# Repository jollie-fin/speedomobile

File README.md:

# Introduction

This project goal is to have a fun plateform to showcase the following :

- sensor fusion
- persistence of vision
- spatial pollution measurement
- video stream enhancement
- non trivial Rust project
- PCB design

It consists, in a way, in a "let's put every components I can find" kind of project

# Firmware

To be done

# 3D printing

Some care will be taken to properly protect components from the rain

To be done

# Hardware

On the hardware side, four boards have been designed

## Main board

This board contain the main MCU, and display the following features :

- 9DOF IMU
- high resolution GPS (ublox M9N)
- Brake sensor
- Ambiant light measurement
- Wheel speed measurement
- Communication with TSDZ2 motor
- I2C expansion connector
- Communication with power board
- Connector for remote control buttons

This board could/should have been a 4 layer board, but I wanted to try the interesting challenge of providing low impedance ground connection with only two layer. Fortunately, besides the GPS antenna, every signal here is low frequency.

## Power board

This board transforms and distributes high voltage from the battery to low 5V voltage.

It also :

- measures battery usage
- protects every connection through PTC fuses
- provides SPI connexion for APA102 led strip
- provides switched 5V connector

Carrying 72A over a 35um pcb is hard. My design choice is to solder copper braid over the back of the board to carry this current. That way, low impedance connection can be done at a cheap price.

## Main I2C board

This board simply connect to the I2C bus the following :

- An I2C LCD (20x4)
- An RFID reader
- Two rotary encoder, through an I2C expander

This board will be the main way to interact with the main board, besides WIFI

## Air quality measurement I2C board

This board simply connect to the I2C bus the following :

- A Temperature/Pressure/Humidity/VOC BME680 sensor
- A PM2.5 sensor

It aims at providing high quality information about the air around the bike

## Blinkers

### Front blinker

A matrix of addressable LED on a flexible PCB, to be glued behind my wing-mirrors

Top and bottom views are the same but mirrored, so that the same pcb can be used left and right

### Side blinker

This board is designed to be chained to form an arch, that will follow the arch of my mudguards. It's a simple chain of addressable leds.

Features some curvy tracks, for more fun in tracing !

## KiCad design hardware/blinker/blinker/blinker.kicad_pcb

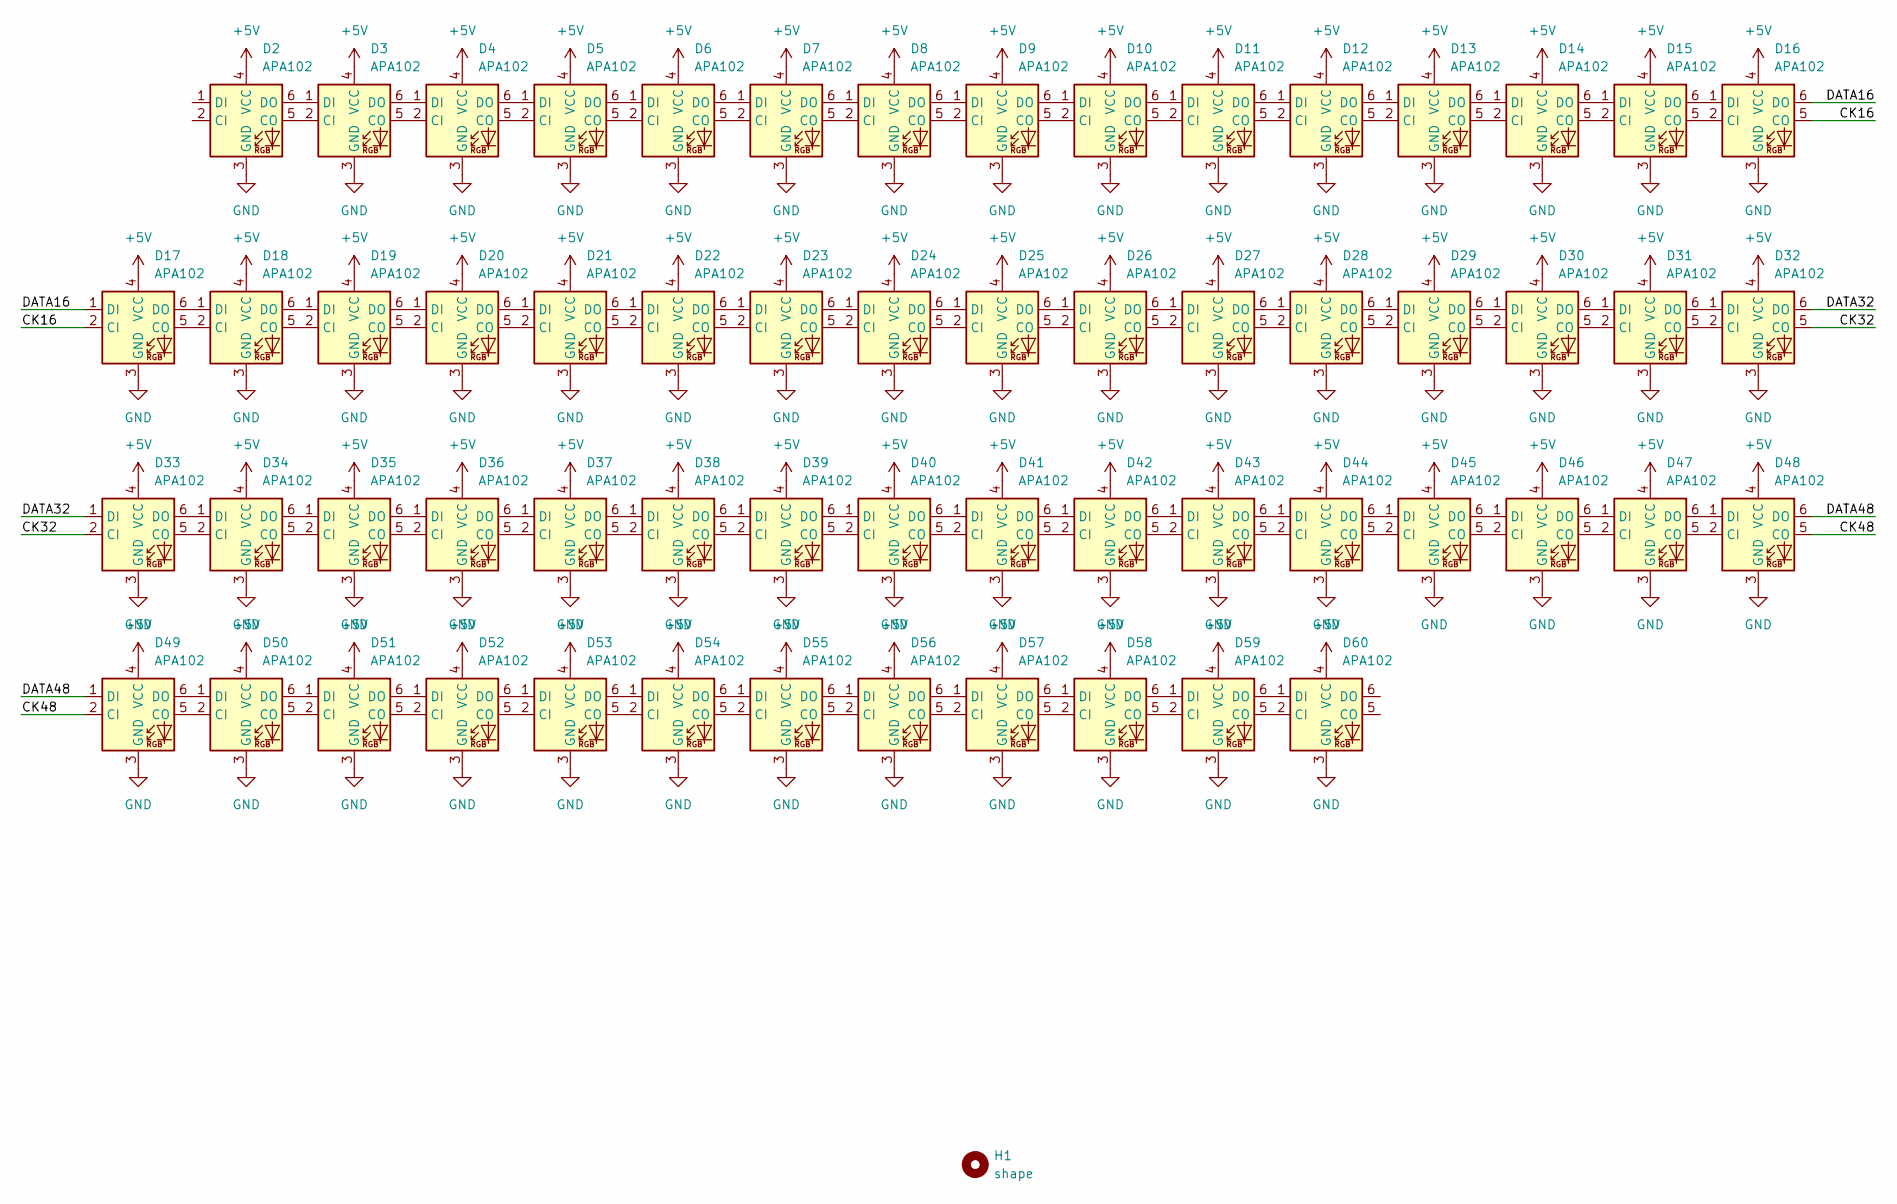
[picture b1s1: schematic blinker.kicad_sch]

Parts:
D2, D3, D4, D5, D6, D7, D8, D9, D10, D11, D12, D13, D14, D15, D16, D17, D18, D19, D20, D21, D22, D23, D24, D25, D26, D27, D28, D29, D30, D31, D32, D33, D34, D35, D36, D37, D38, D39, D40, D41, D42, D43, D44, D45, D46, D47, D48, D49, D50, D51, D52, D53, D54, D55, D56, D57, D58, D59, D60: APA102; LED_RGB_5050-6
H1: shape; blinker_shape

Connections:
+5V: D2.4 (VCC), D3.4 (VCC), D4.4 (VCC), D5.4 (VCC), D6.4 (VCC), D7.4 (VCC), D8.4 (VCC), D9.4 (VCC), D10.4 (VCC), D11.4 (VCC), D12.4 (VCC), D13.4 (VCC), D14.4 (VCC), D15.4 (VCC), D16.4 (VCC), D17.4 (VCC), D18.4 (VCC), D19.4 (VCC), D20.4 (VCC), D21.4 (VCC), D22.4 (VCC), D23.4 (VCC), D24.4 (VCC), D25.4 (VCC), D26.4 (VCC), D27.4 (VCC), D28.4 (VCC), D29.4 (VCC), D30.4 (VCC), D31.4 (VCC), D32.4 (VCC), D33.4 (VCC), D34.4 (VCC), D35.4 (VCC), D36.4 (VCC), D37.4 (VCC), D38.4 (VCC), D39.4 (VCC), D40.4 (VCC), D41.4 (VCC), D42.4 (VCC), D43.4 (VCC), D44.4 (VCC), D45.4 (VCC), D46.4 (VCC), D47.4 (VCC), D48.4 (VCC), D49.4 (VCC), D50.4 (VCC), D51.4 (VCC), D52.4 (VCC), D53.4 (VCC), D54.4 (VCC), D55.4 (VCC), D56.4 (VCC), D57.4 (VCC), D58.4 (VCC), D59.4 (VCC), D60.4 (VCC)
/CK16: D16.5 (CO), D17.2 (CI)
/CK32: D32.5 (CO), D33.2 (CI)
/CK48: D48.5 (CO), D49.2 (CI)
/DATA16: D16.6 (DO), D17.1 (DI)
/DATA32: D32.6 (DO), D33.1 (DI)
/DATA48: D48.6 (DO), D49.1 (DI)
GND: D2.3 (GND), D3.3 (GND), D4.3 (GND), D5.3 (GND), D6.3 (GND), D7.3 (GND), D8.3 (GND), D9.3 (GND), D10.3 (GND), D11.3 (GND), D12.3 (GND), D13.3 (GND), D14.3 (GND), D15.3 (GND), D16.3 (GND), D17.3 (GND), D18.3 (GND), D19.3 (GND), D20.3 (GND), D21.3 (GND), D22.3 (GND), D23.3 (GND), D24.3 (GND), D25.3 (GND), D26.3 (GND), D27.3 (GND), D28.3 (GND), D29.3 (GND), D30.3 (GND), D31.3 (GND), D32.3 (GND), D33.3 (GND), D34.3 (GND), D35.3 (GND), D36.3 (GND), D37.3 (GND), D38.3 (GND), D39.3 (GND), D40.3 (GND), D41.3 (GND), D42.3 (GND), D43.3 (GND), D44.3 (GND), D45.3 (GND), D46.3 (GND), D47.3 (GND), D48.3 (GND), D49.3 (GND), D50.3 (GND), D51.3 (GND), D52.3 (GND), D53.3 (GND), D54.3 (GND), D55.3 (GND), D56.3 (GND), D57.3 (GND), D58.3 (GND), D59.3 (GND), D60.3 (GND)
unnamed: D2.5 (CO), D3.2 (CI)
unnamed: D2.6 (DO), D3.1 (DI)
unnamed: D3.5 (CO), D4.2 (CI)
unnamed: D3.6 (DO), D4.1 (DI)
unnamed: D4.5 (CO), D5.2 (CI)
unnamed: D4.6 (DO), D5.1 (DI)
unnamed: D5.5 (CO), D6.2 (CI)
unnamed: D5.6 (DO), D6.1 (DI)
unnamed: D6.5 (CO), D7.2 (CI)
unnamed: D6.6 (DO), D7.1 (DI)
unnamed: D7.5 (CO), D8.2 (CI)
unnamed: D7.6 (DO), D8.1 (DI)
unnamed: D8.5 (CO), D9.2 (CI)
unnamed: D8.6 (DO), D9.1 (DI)
unnamed: D9.5 (CO), D10.2 (CI)
unnamed: D10.5 (CO), D11.2 (CI)
unnamed: D9.6 (DO), D10.1 (DI)
unnamed: D10.6 (DO), D11.1 (DI)
unnamed: D11.5 (CO), D12.2 (CI)
unnamed: D11.6 (DO), D12.1 (DI)
unnamed: D12.5 (CO), D13.2 (CI)
unnamed: D12.6 (DO), D13.1 (DI)
unnamed: D13.5 (CO), D14.2 (CI)
unnamed: D13.6 (DO), D14.1 (DI)
unnamed: D14.5 (CO), D15.2 (CI)
unnamed: D14.6 (DO), D15.1 (DI)
unnamed: D15.5 (CO), D16.2 (CI)
unnamed: D15.6 (DO), D16.1 (DI)
unnamed: D17.5 (CO), D18.2 (CI)
unnamed: D17.6 (DO), D18.1 (DI)
unnamed: D18.5 (CO), D19.2 (CI)
unnamed: D18.6 (DO), D19.1 (DI)
unnamed: D19.5 (CO), D20.2 (CI)
unnamed: D19.6 (DO), D20.1 (DI)
unnamed: D20.5 (CO), D21.2 (CI)
unnamed: D20.6 (DO), D21.1 (DI)
unnamed: D21.5 (CO), D22.2 (CI)
unnamed: D21.6 (DO), D22.1 (DI)
unnamed: D22.5 (CO), D23.2 (CI)
unnamed: D22.6 (DO), D23.1 (DI)
unnamed: D23.5 (CO), D24.2 (CI)
unnamed: D23.6 (DO), D24.1 (DI)
unnamed: D24.5 (CO), D25.2 (CI)
unnamed: D24.6 (DO), D25.1 (DI)
unnamed: D25.5 (CO), D26.2 (CI)
unnamed: D25.6 (DO), D26.1 (DI)
unnamed: D26.5 (CO), D27.2 (CI)
unnamed: D26.6 (DO), D27.1 (DI)
unnamed: D27.5 (CO), D28.2 (CI)
unnamed: D27.6 (DO), D28.1 (DI)
unnamed: D28.5 (CO), D29.2 (CI)
unnamed: D28.6 (DO), D29.1 (DI)
unnamed: D29.5 (CO), D30.2 (CI)
unnamed: D29.6 (DO), D30.1 (DI)
unnamed: D30.5 (CO), D31.2 (CI)
unnamed: D30.6 (DO), D31.1 (DI)
unnamed: D31.5 (CO), D32.2 (CI)
unnamed: D31.6 (DO), D32.1 (DI)
unnamed: D33.5 (CO), D34.2 (CI)
unnamed: D33.6 (DO), D34.1 (DI)
unnamed: D34.5 (CO), D35.2 (CI)
unnamed: D34.6 (DO), D35.1 (DI)
unnamed: D35.5 (CO), D36.2 (CI)
unnamed: D35.6 (DO), D36.1 (DI)
unnamed: D36.5 (CO), D37.2 (CI)
unnamed: D36.6 (DO), D37.1 (DI)
unnamed: D37.5 (CO), D38.2 (CI)
unnamed: D37.6 (DO), D38.1 (DI)
unnamed: D38.5 (CO), D39.2 (CI)
unnamed: D38.6 (DO), D39.1 (DI)
unnamed: D39.5 (CO), D40.2 (CI)
unnamed: D39.6 (DO), D40.1 (DI)
unnamed: D40.5 (CO), D41.2 (CI)
unnamed: D40.6 (DO), D41.1 (DI)
unnamed: D41.5 (CO), D42.2 (CI)
unnamed: D41.6 (DO), D42.1 (DI)
unnamed: D42.5 (CO), D43.2 (CI)
unnamed: D42.6 (DO), D43.1 (DI)
unnamed: D43.5 (CO), D44.2 (CI)
unnamed: D43.6 (DO), D44.1 (DI)
unnamed: D44.5 (CO), D45.2 (CI)
unnamed: D44.6 (DO), D45.1 (DI)
unnamed: D45.5 (CO), D46.2 (CI)
unnamed: D45.6 (DO), D46.1 (DI)
unnamed: D46.5 (CO), D47.2 (CI)
unnamed: D46.6 (DO), D47.1 (DI)
unnamed: D47.5 (CO), D48.2 (CI)
unnamed: D47.6 (DO), D48.1 (DI)
unnamed: D49.5 (CO), D50.2 (CI)
unnamed: D49.6 (DO), D50.1 (DI)
unnamed: D50.5 (CO), D51.2 (CI)
unnamed: D50.6 (DO), D51.1 (DI)
unnamed: D51.5 (CO), D52.2 (CI)
unnamed: D51.6 (DO), D52.1 (DI)
unnamed: D52.5 (CO), D53.2 (CI)
unnamed: D52.6 (DO), D53.1 (DI)
unnamed: D53.5 (CO), D54.2 (CI)
unnamed: D53.6 (DO), D54.1 (DI)
unnamed: D54.5 (CO), D55.2 (CI)
unnamed: D54.6 (DO), D55.1 (DI)
unnamed: D55.5 (CO), D56.2 (CI)
unnamed: D55.6 (DO), D56.1 (DI)
unnamed: D56.5 (CO), D57.2 (CI)
unnamed: D56.6 (DO), D57.1 (DI)
unnamed: D57.5 (CO), D58.2 (CI)
unnamed: D57.6 (DO), D58.1 (DI)
unnamed: D58.5 (CO), D59.2 (CI)
unnamed: D58.6 (DO), D59.1 (DI)
unnamed: D59.5 (CO), D60.2 (CI)
unnamed: D59.6 (DO), D60.1 (DI)

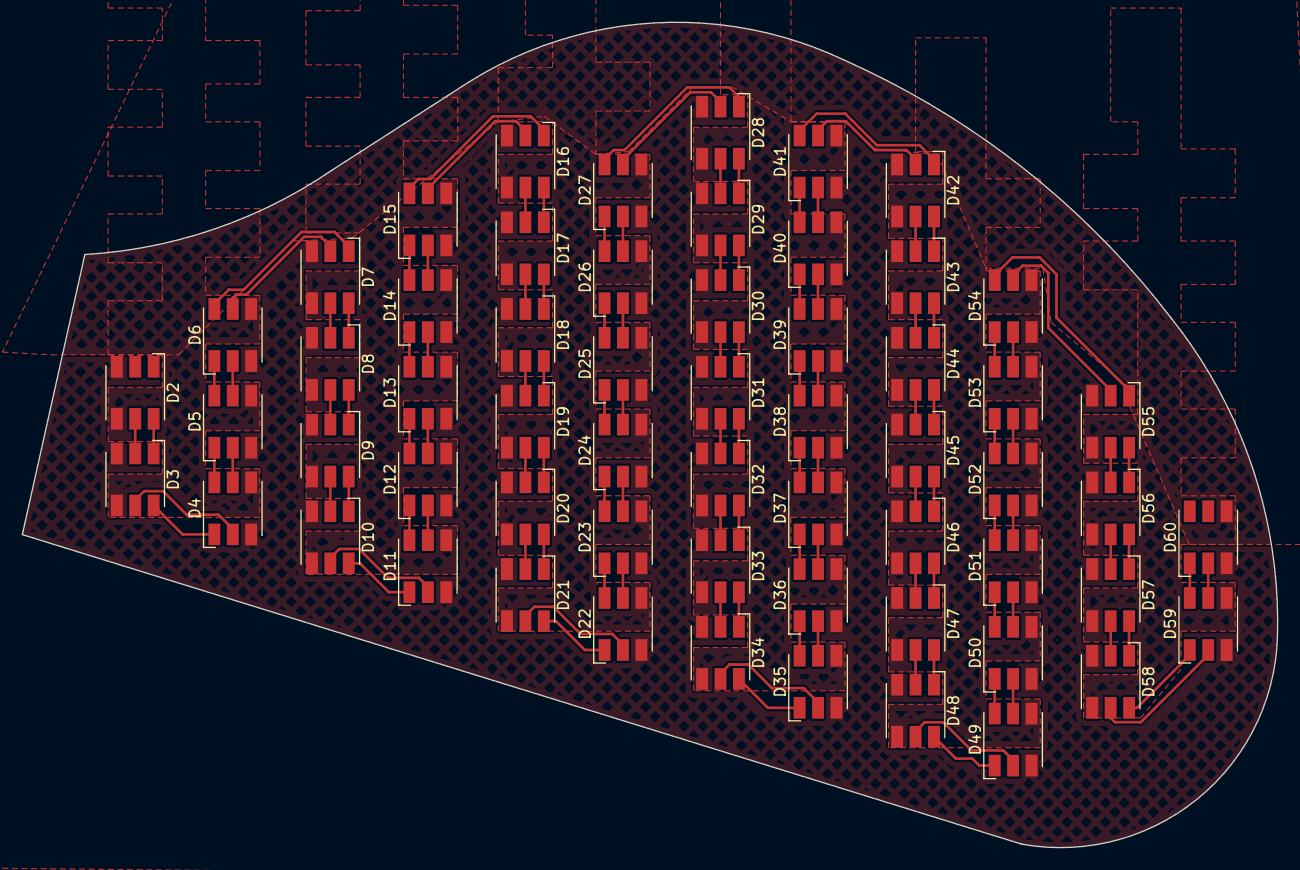
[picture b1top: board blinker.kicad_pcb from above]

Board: 2 copper layers, 115.8 x 76.1 mm, 60 parts (0 on the bottom side), 118 nets.

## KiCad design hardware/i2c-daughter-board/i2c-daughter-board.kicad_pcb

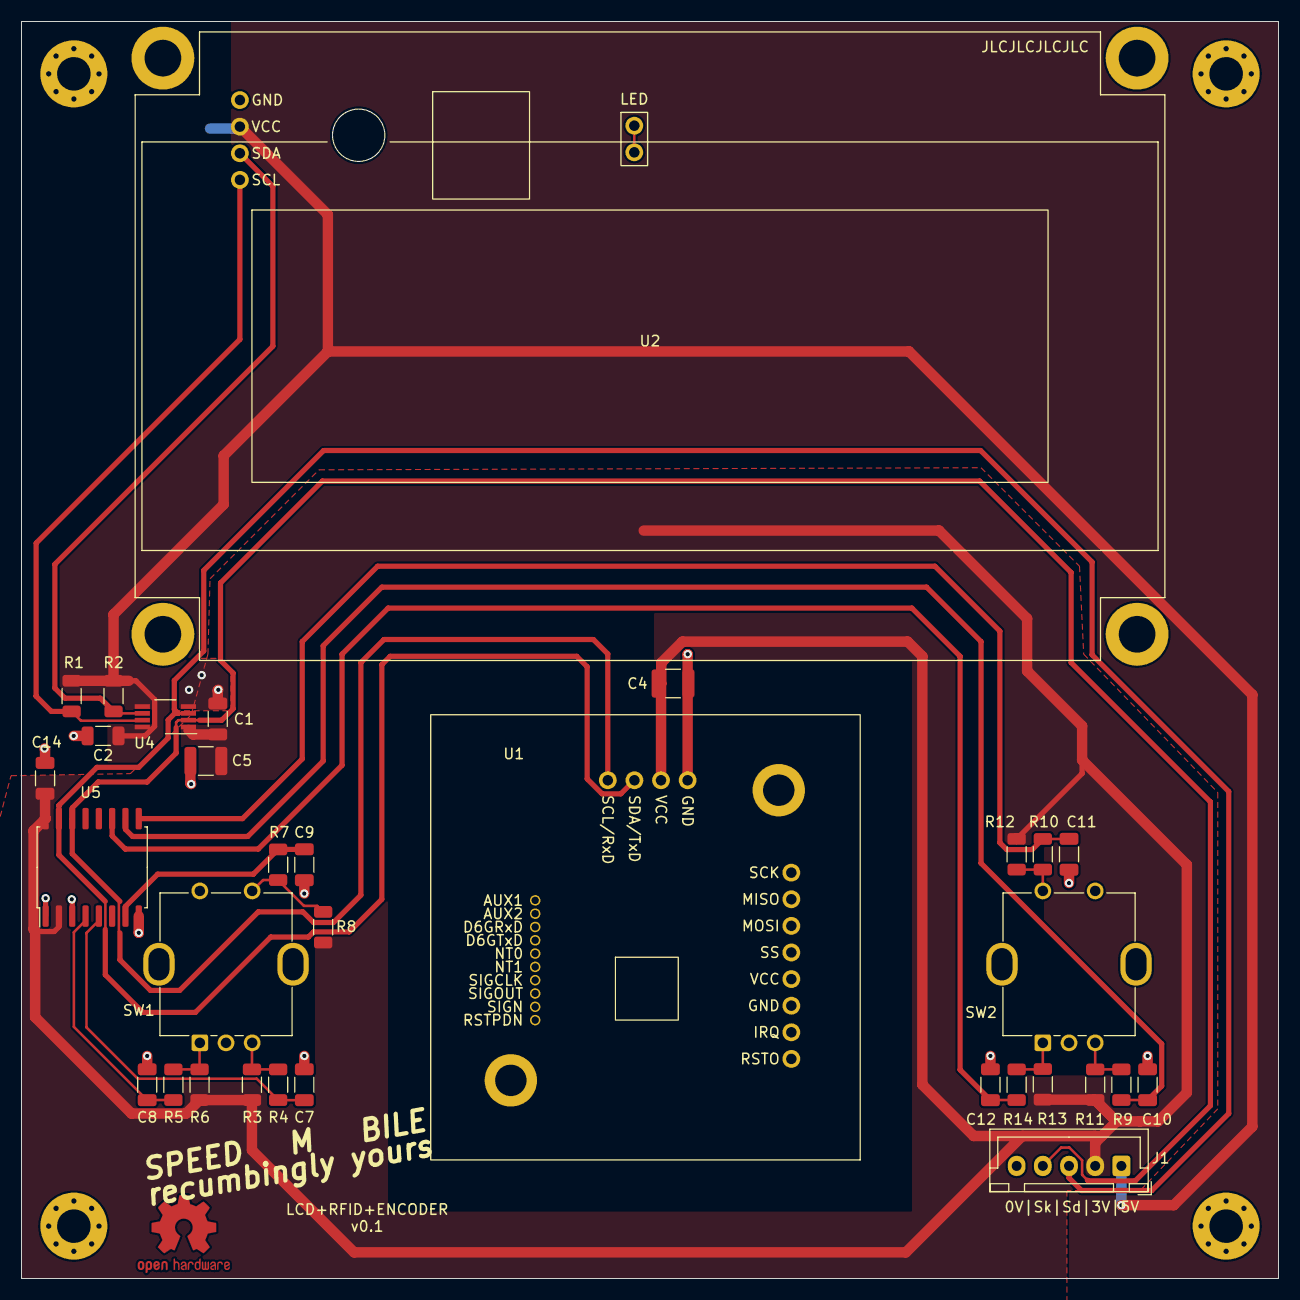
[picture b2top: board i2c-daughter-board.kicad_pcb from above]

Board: 2 copper layers, 120.0 x 120.0 mm, 38 parts (1 on the bottom side), 20 nets.

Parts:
C1, C2, C14: 100n; C_1206_3216Metric
C4, C5, C6: 22u; C_1210_3225Metric
C7, C8, C9, C10, C11, C12: 10n; C_1206_3216Metric
H1, H2, H3, H4: M3; MountingHole_3.2mm_M3_Pad_Via
J1: Conn_01x05; JST_XH_B5B-XH-A_1x05_P2.50mm_Vertical
R1, R2: 4k7; R_1206_3216Metric
R3, R4, R5, R6, R7, R8, R9, R10, R11, R12, R13, R14: 10k; R_1206_3216Metric
SW1, SW2: PEC11H; RotaryEncoder_Bourns_Vertical_PEC11H-4xxxF-Sxxxx
SYMB1: OSHW; OSHW-Logo2_9.8x8mm_Mask
U1: PN532
U2: HD44780_PCF8574T
U4: TCA9617A; VSSOP-8_3.0x3.0mm_P0.65mm
U5: PCF8574; SOIC-16W_7.5x10.3mm_P1.27mm

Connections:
+3V3: C1.1, C4.1, C5.1, C14.1, J1.2, R3.1, R6.1, R8.1, R11.1, R12.1, R13.1, U1.2 (VCC), U4.1 (VCCA), U5.2 (A1), U5.16 (VDD)
+5V: C2.1, C6.1, J1.1, R1.1, R2.1, U2.2 (VCC), U4.5 (EN), U4.8 (VCCB)
/ENCA0: C8.1, R5.1, U5.4 (P0)
/ENCA1: C12.1, R14.1, U5.11 (P6)
/ENCB0: C7.1, R4.1, U5.5 (P1)
/ENCB1: C10.1, R9.1, U5.10 (P5)
/ENCSW0: C9.1, R7.1, U5.7 (P3)
/ENCSW1: C11.1, R10.1, U5.9 (P4)
/SCL: J1.4, U1.4 (SCL), U4.2 (SCLA), U5.14 (SCL)
/SCL_5V: R1.2, U2.4 (SCL), U4.7 (SCLB)
/SDA: J1.3, U1.3 (SDA), U4.3 (SDAA), U5.15 (SDA)
/SDA_5V: R2.2, U2.3 (SDA), U4.6 (SDAB)
GND: C1.2, C2.2, C4.2, C5.2, C6.2, C7.2, C8.2, C9.2, C10.2, C11.2, C12.2, C14.2, H1.1, H2.1, H3.1, H4.1, J1.5, SW1.C, SW1.S1, SW1.SH (S2), SW2.C, SW2.S2, SW2.SH (S2), U1.1 (GND), U2.1 (GND), U4.4 (GND), U5.1 (A0), U5.3 (A2), U5.8 (VSS)
unnamed: R3.2, R4.2, SW1.B
unnamed: R5.2, R6.2, SW1.A
unnamed: R7.2, R8.2, SW1.S2
unnamed: R10.2, R12.2, SW2.S1
unnamed: R9.2, R11.2, SW2.B
unnamed: R13.2, R14.2, SW2.A
unnamed: U2.5 (LED), U2.6 (LED)

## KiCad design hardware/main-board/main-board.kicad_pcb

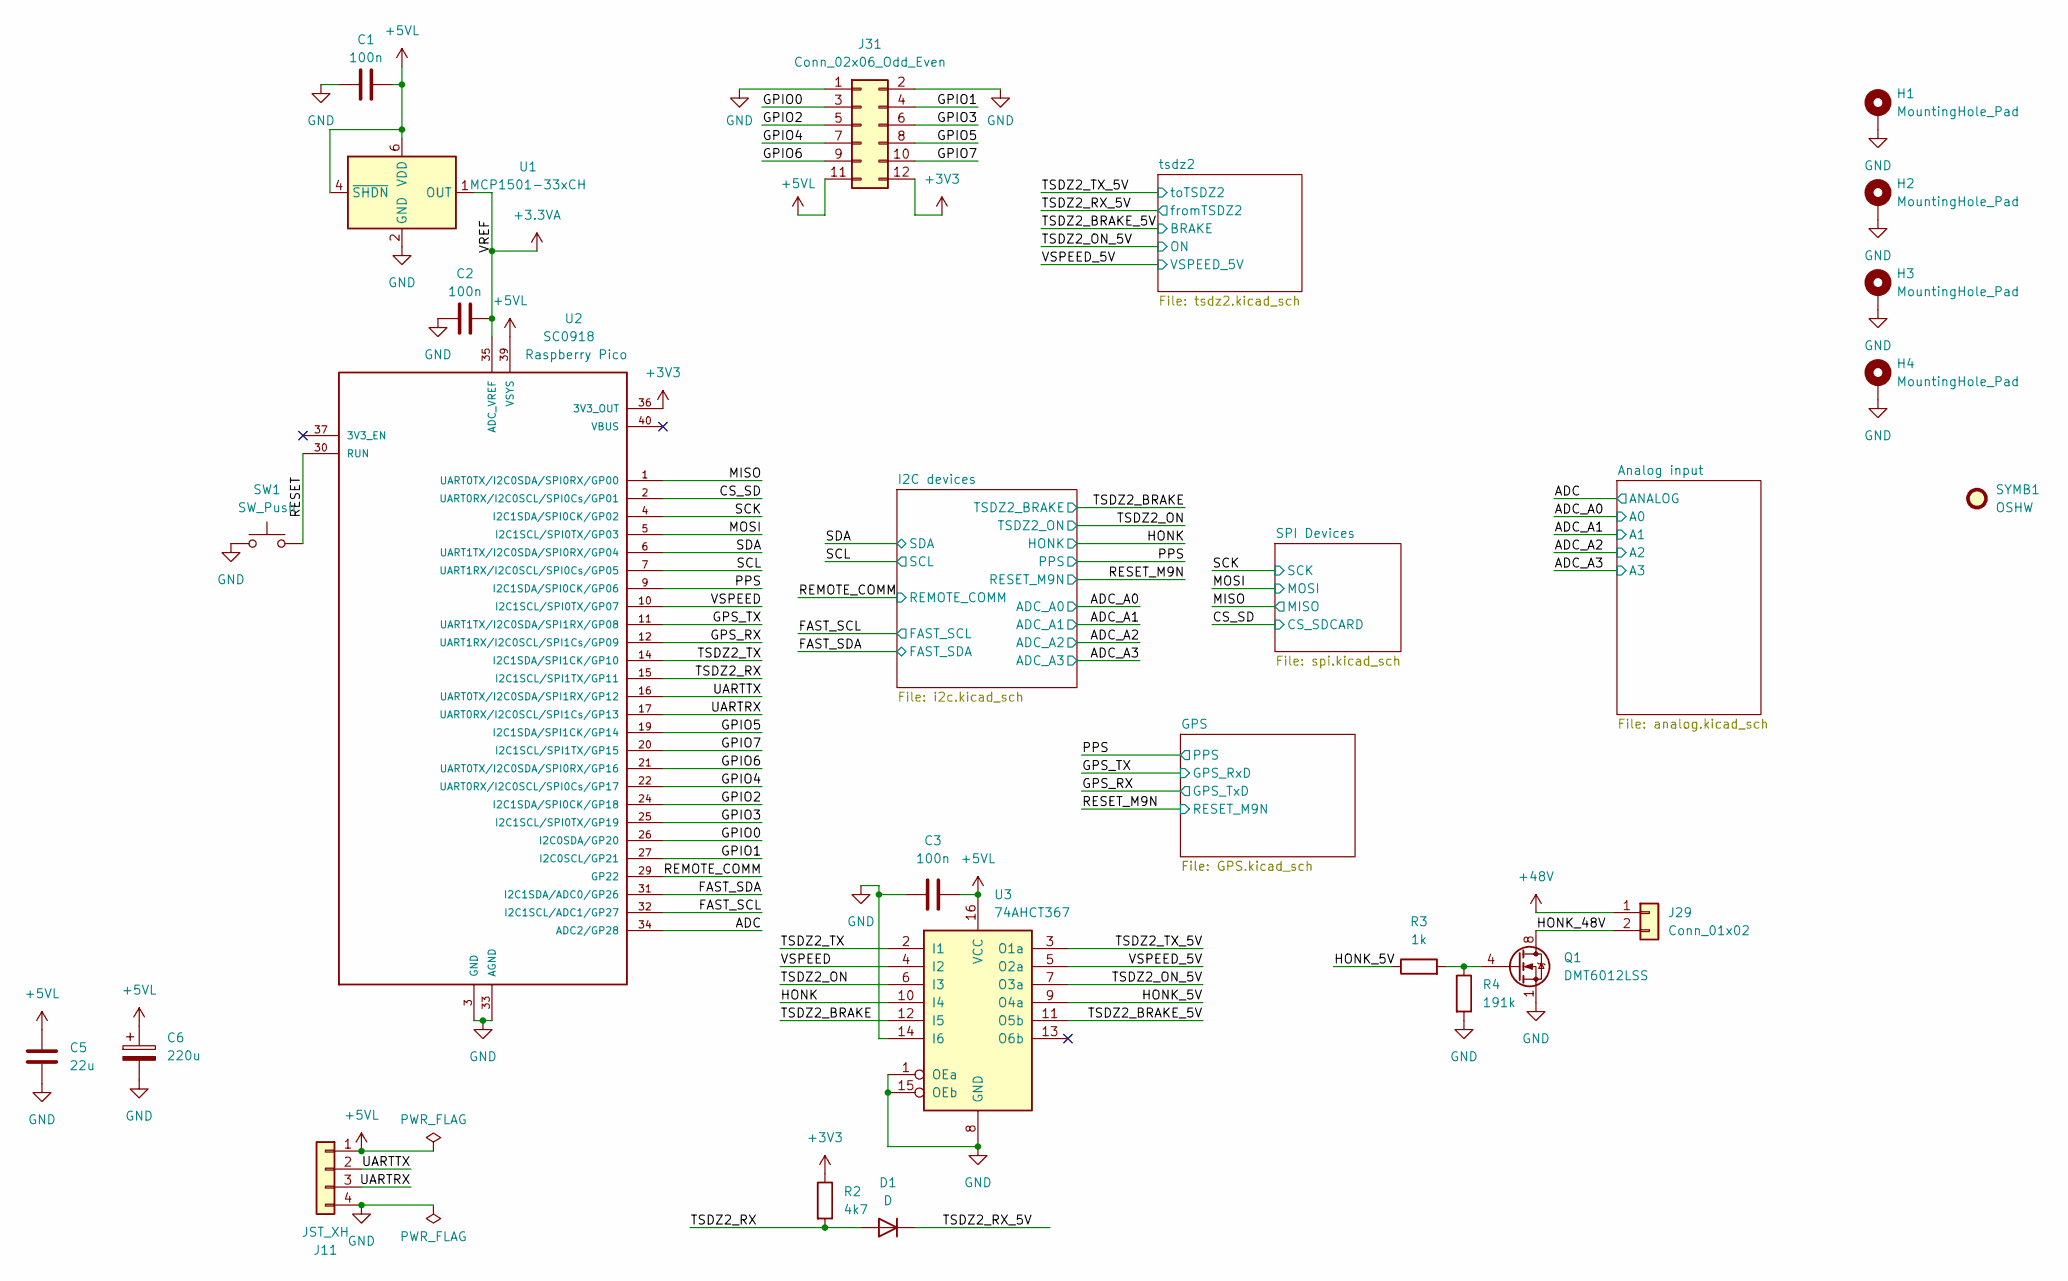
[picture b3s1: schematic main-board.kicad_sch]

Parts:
C1, C2, C3: 100n; C_1206_3216Metric; mouser 80-C1206C104K5R
C5: 22u; C_1210_3225Metric; Mouser CL32B226MOJNNNE
C6: 220u; CP_Radial_D16.0mm_P7.50mm; Mouser EKY-101ELL221ML20S
D1: D; D_1206_3216Metric; mouser 581-SD1206S040S0R5
H1, H2, H3, H4: MountingHole_Pad; MountingHole_3.2mm_M3_Pad_Via
J11: JST_XH; JST_XH_B4B-XH-A_1x04_P2.50mm_Vertical
J29: Conn_01x02; JST_XH_B2B-XH-A_1x02_P2.50mm_Vertical
J31: Conn_02x06_Odd_Even; IDC-Header_2x06_P2.54mm_Vertical; mouser 538-90130-1112
Q1: DMT6012LSS; SOIC-8_3.9x4.9mm_P1.27mm; mouser 621-DMT6012LSS-13
R2: 4k7; R_1206_3216Metric; mouser 791-WR12X4701FTL
R3: 1k; R_1206_3216Metric; mouser 603-AC1206FR-101KL
R4: 191k; R_1206_3216Metric; mouser 660-RK73H2BTTD1913F
SW1: SW_Push; SW_PUSH_6mm; mouser 179-TS026650BK100LCR
SYMB1: OSHW; OSHW-Logo2_9.8x8mm_Mask
U1: MCP1501-33xCH; SOT-23-6; mouser 579-MCP1501-33E/SN
U2: SC0918; MODULE_SC0918; PARTREV 1.6
U3: 74AHCT367; SOIC-16_3.9x9.9mm_P1.27mm; mouser 595-SN74AHCT367DR

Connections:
+3.3VA: C2.2, U1.1 (OUT), U2.35 (ADC_VREF)
+3V3: J31.12, R2.1, U2.36 (3V3_OUT); also elsewhere on the board
+5VL: C1.2, C3.1, C5.1, C6.1, J11.1, J31.11, U1.4 (~SHDN), U1.6 (VDD), U2.39 (VSYS), U3.16 (VCC); also elsewhere on the board
+48V: J29.1; also elsewhere on the board
/ADC: U2.34 (ADC2/GP28); also elsewhere on the board
/CS_SD: U2.2 (UART0RX/I2C0SCL/SPI0Cs/GP01); also elsewhere on the board
/FAST_SCL: U2.32 (I2C1SCL/ADC1/GP27); also elsewhere on the board
/FAST_SDA: U2.31 (I2C1SDA/ADC0/GP26); also elsewhere on the board
/GPIO0: J31.3, U2.26 (I2C0SDA/GP20)
/GPIO1: J31.4, U2.27 (I2C0SCL/GP21)
/GPIO2: J31.5, U2.24 (I2C1SDA/SPI0CK/GP18)
/GPIO3: J31.6, U2.25 (I2C1SCL/SPI0TX/GP19)
/GPIO4: J31.7, U2.22 (UART0RX/I2C0SCL/SPI0Cs/GP17)
/GPIO5: J31.8, U2.19 (I2C1SDA/SPI1CK/GP14)
/GPIO6: J31.9, U2.21 (UART0TX/I2C0SDA/SPI0RX/GP16)
/GPIO7: J31.10, U2.20 (I2C1SCL/SPI1TX/GP15)
/GPS_RX: U2.12 (UART1RX/I2C0SCL/SPI1Cs/GP09); also elsewhere on the board
/GPS_TX: U2.11 (UART1TX/I2C0SDA/SPI1RX/GP08); also elsewhere on the board
/HONK: U3.10 (I4); also elsewhere on the board
/HONK_5V: R3.1, U3.9 (O4a)
/HONK_48V: J29.2, Q1.5 (D), Q1.6 (D), Q1.7 (D), Q1.8 (D)
/MISO: U2.1 (UART0TX/I2C0SDA/SPI0RX/GP00); also elsewhere on the board
/MOSI: U2.5 (I2C1SCL/SPI0TX/GP03); also elsewhere on the board
/PPS: U2.9 (I2C1SDA/SPI0CK/GP06); also elsewhere on the board
/RESET: SW1.2, U2.30 (RUN)
/SCK: U2.4 (I2C1SDA/SPI0CK/GP02); also elsewhere on the board
/SCL: U2.7 (UART1RX/I2C0SCL/SPI0Cs/GP05); also elsewhere on the board
/SDA: U2.6 (UART1TX/I2C0SDA/SPI0RX/GP04); also elsewhere on the board
/TSDZ2_BRAKE: U3.12 (I5); also elsewhere on the board
/TSDZ2_BRAKE_5V: U3.11 (O5b); also elsewhere on the board
/TSDZ2_ON: U3.6 (I3); also elsewhere on the board
/TSDZ2_ON_5V: U3.7 (O3a); also elsewhere on the board
/TSDZ2_RX: D1.2 (A), R2.2, U2.15 (I2C1SCL/SPI1TX/GP11)
/TSDZ2_RX_5V: D1.1 (K); also elsewhere on the board
/TSDZ2_TX: U2.14 (I2C1SDA/SPI1CK/GP10), U3.2 (I1)
/TSDZ2_TX_5V: U3.3 (O1a); also elsewhere on the board
/UARTRX: J11.3, U2.17 (UART0RX/I2C0SCL/SPI1Cs/GP13)
/UARTTX: J11.2, U2.16 (UART0TX/I2C0SDA/SPI1RX/GP12)
/VSPEED: U2.10 (I2C1SCL/SPI0TX/GP07), U3.4 (I2)
/VSPEED_5V: U3.5 (O2a); also elsewhere on the board
GND: C1.1, C2.1, C3.2, C5.2, C6.2, H1.1, H2.1, H3.1, H4.1, J11.4, J31.1, J31.2, Q1.1 (S), Q1.2 (S), Q1.3 (S), R4.2, SW1.1, U1.2 (GND), U1.3 (GND), U1.5 (GND), U2.3 (GND), U2.8 (GND), U2.13 (GND), U2.18 (GND), U2.23 (GND), U2.28 (GND), U2.33 (AGND), U2.38 (GND), U2.M1 (GND), U2.M2 (GND), U2.M3 (GND), U2.M4 (GND), U3.1 (OEa), U3.8 (GND), U3.14 (I6), U3.15 (OEb); also elsewhere on the board
unnamed: Q1.4 (G), R3.2, R4.1

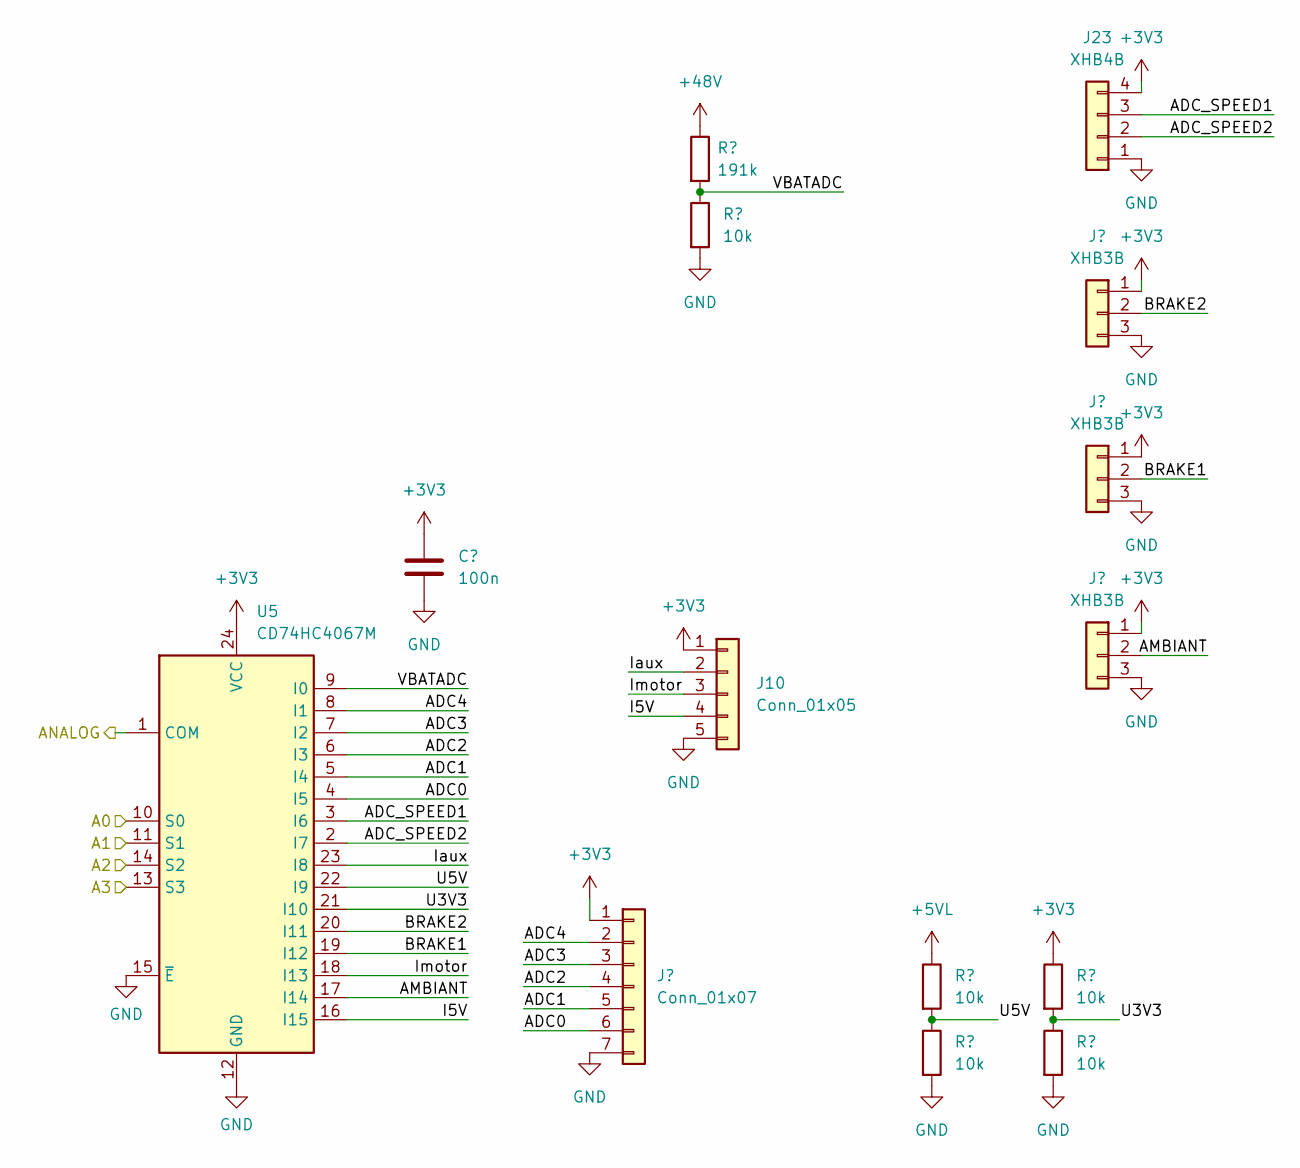
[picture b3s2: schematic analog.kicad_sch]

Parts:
C4: 100n; C_1206_3216Metric; mouser 80-C1206C104K5R
J7: Conn_01x07; JST_XH_B7B-XH-A_1x07_P2.50mm_Vertical
J10: Conn_01x05; JST_XH_B5B-XH-A_1x05_P2.50mm_Vertical
J23: XHB4B; JST_XH_B4B-XH-A_1x04_P2.50mm_Vertical
J24, J25, J26: XHB3B; JST_XH_B3B-XH-A_1x03_P2.50mm_Vertical
R7: 191k; R_1206_3216Metric; mouser 660-RK73H2BTTD1913F
R8, R10, R11, R12, R13: 10k; R_1206_3216Metric; mouser 603-AC1206FR-0710KL
U5: CD74HC4067M; SOIC-24W_7.5x15.4mm_P1.27mm; mouser 771-74HC4067PW-T

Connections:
+3V3: C4.1, J7.1, J10.1, J23.4, J24.1, J25.1, J26.1, R12.1, U5.24 (VCC); also elsewhere on the board
+5VL: R10.1; also elsewhere on the board
+48V: R7.1; also elsewhere on the board
/ADC: U5.1 (COM); also elsewhere on the board
/ADC_A0: U5.10 (S0); also elsewhere on the board
/ADC_A1: U5.11 (S1); also elsewhere on the board
/ADC_A2: U5.14 (S2); also elsewhere on the board
/ADC_A3: U5.13 (S3); also elsewhere on the board
/Analog input/ADC_SPEED1: J23.3, U5.3 (I6)
/Analog input/ADC_SPEED2: J23.2, U5.2 (I7)
/Analog input/AMBIANT: J26.2, U5.17 (I14)
/Analog input/BRAKE1: J25.2, U5.19 (I12)
/Analog input/BRAKE2: J24.2, U5.20 (I11)
/Analog input/I5V: J10.4, U5.16 (I15)
/Analog input/Iaux: J10.2, U5.23 (I8)
/Analog input/Imotor: J10.3, U5.18 (I13)
/Analog input/U3V3: R12.2, R13.1, U5.21 (I10)
/Analog input/U5V: R10.2, R11.1, U5.22 (I9)
/Analog input/VBATADC: R7.2, R8.1, U5.9 (I0)
GND: C4.2, J7.7, J10.5, J23.1, J24.3, J25.3, J26.3, R8.2, R11.2, R13.2, U5.12 (GND), U5.15 (~E); also elsewhere on the board

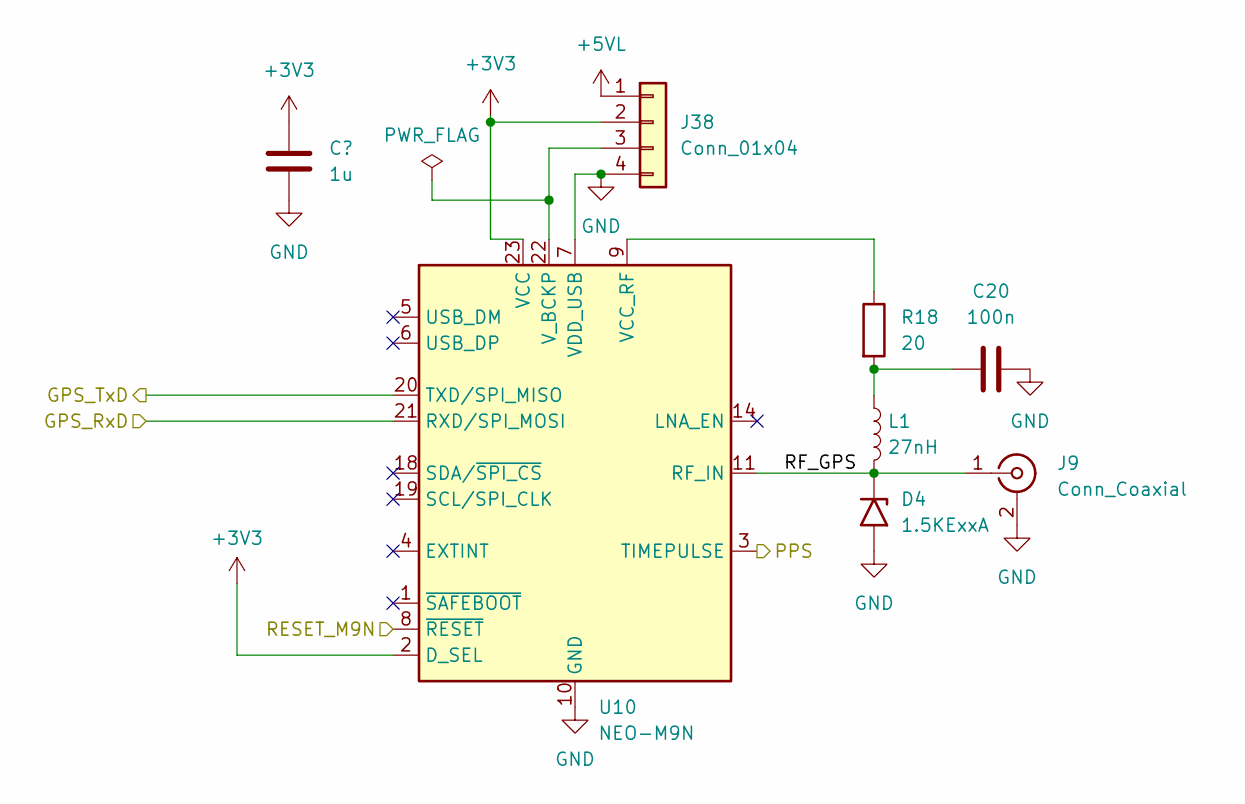
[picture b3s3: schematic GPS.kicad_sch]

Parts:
C19: 1u; C_1206_3216Metric; mouser 187-CL31B105KBHNFNE
C20: 100n; C_0603_1608Metric; mouser 187-CL10B104KA8NNWC
D4: 1.5KExxA; D_0603_1608Metric; mouser 652-CG0603MLU-05E
J9: Conn_Coaxial; U.FL_Hirose_U.FL-R-SMT-1_Vertical; mouser 798-U.FL-R-SMT10
J38: Conn_01x04; JST_XH_B4B-XH-A_1x04_P2.50mm_Vertical
L1: 27nH; L_0603_1608Metric; mouser 871-B82496C3270J
R18: 20; R_0603_1608Metric; mouser 660-SG73P1JTTD20R0F
U10: NEO-M9N; ublox_NEO; mouser 377-NEO-M9N-00B

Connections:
/GPS/RF_GPS: D4.1 (A1), J9.1 (In), L1.2; also elsewhere on the board
GND: D4.2 (A2), J9.2 (Ext); also elsewhere on the board
unnamed 62: L1.1; also elsewhere on the board

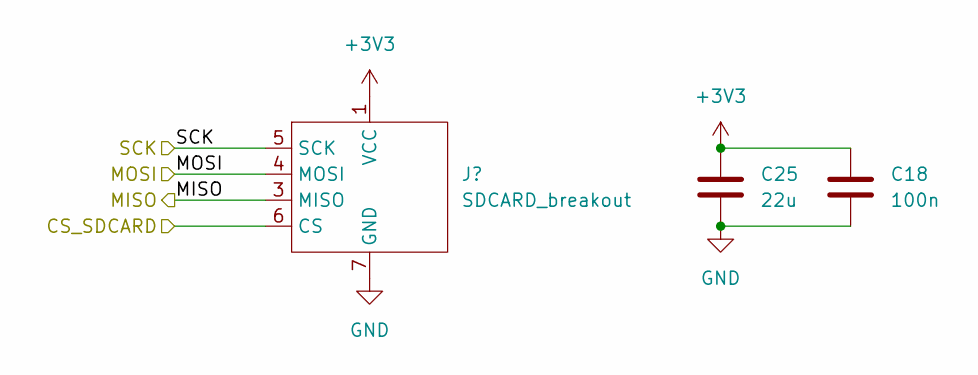
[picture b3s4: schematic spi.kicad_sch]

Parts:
C18: 100n; C_1206_3216Metric; mouser 80-C1206C104K5R
C25: 22u; C_1210_3225Metric; Mouser CL32B226MOJNNNE
J35: SDCARD_breakout; sdcard

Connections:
+3V3: C18.1, C25.1, J35.1 (VCC); also elsewhere on the board
/CS_SD: J35.6 (CS); also elsewhere on the board
/MISO: J35.3 (MISO); also elsewhere on the board
/MOSI: J35.4 (MOSI); also elsewhere on the board
/SCK: J35.5 (SCK); also elsewhere on the board
GND: C18.2, C25.2, J35.7 (GND); also elsewhere on the board
